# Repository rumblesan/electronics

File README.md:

# Electronics Projects

KiCAD projects for electronics stuff I'm working on.

## Description

Mostly Serge/CGS synth stuff currently, with all original circuits designed by Serge Tcherepnin and Ken Stone.

## Contact

Drop me an email at guy@rumblesan.com

## License

Creative Commons Attribution 4.0 International License

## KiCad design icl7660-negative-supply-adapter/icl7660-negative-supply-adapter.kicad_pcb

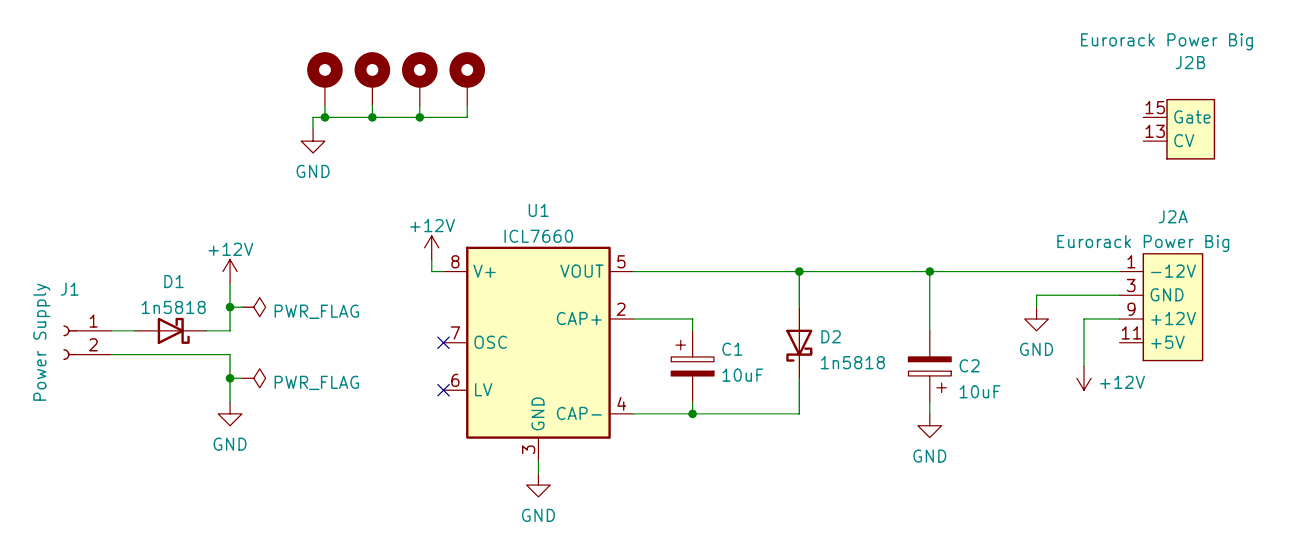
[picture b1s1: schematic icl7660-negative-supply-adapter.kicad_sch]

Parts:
C1, C2: 10uF; CP_Radial_D5.0mm_P2.00mm; Tolerance 20%; Voltage 50v
D1, D2: 1n5818; D_DO-41_SOD81_P10.16mm_Horizontal
H1, H2, H3, H4: MountingHole_Pad; MountingHole_3.2mm_M3_DIN965_Pad
J1: Power Supply; PinHeader_1x02_P2.54mm_Vertical
J2: Eurorack Power Big; Eurorack_PowerHeader_2x08_P2.54mm_Shrouded
U1: ICL7660; DIP-8_W7.62mm_Socket

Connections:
+12V: D1.1 (K), J2.9 (+12V), J2.10 (+12V), U1.8 (V+)
GND: C2.1, H1.1, H2.1, H3.1, H4.1, J1.2, J2.3 (GND), J2.4 (GND), J2.5 (GND), J2.6 (GND), J2.7 (GND), J2.8 (GND), U1.3 (GND)
unnamed: C1.1, U1.2 (CAP+)
unnamed: C1.2, D2.1 (K), U1.4 (CAP-)
unnamed: C2.2, D2.2 (A), J2.1 (-12V), J2.2 (-12V), U1.5 (VOUT)
unnamed: D1.2 (A), J1.1
unnamed: J2.11 (+5V), J2.12 (+5V)
unnamed: J2.13 (CV), J2.14 (CV)
unnamed: J2.15 (Gate), J2.16 (Gate)

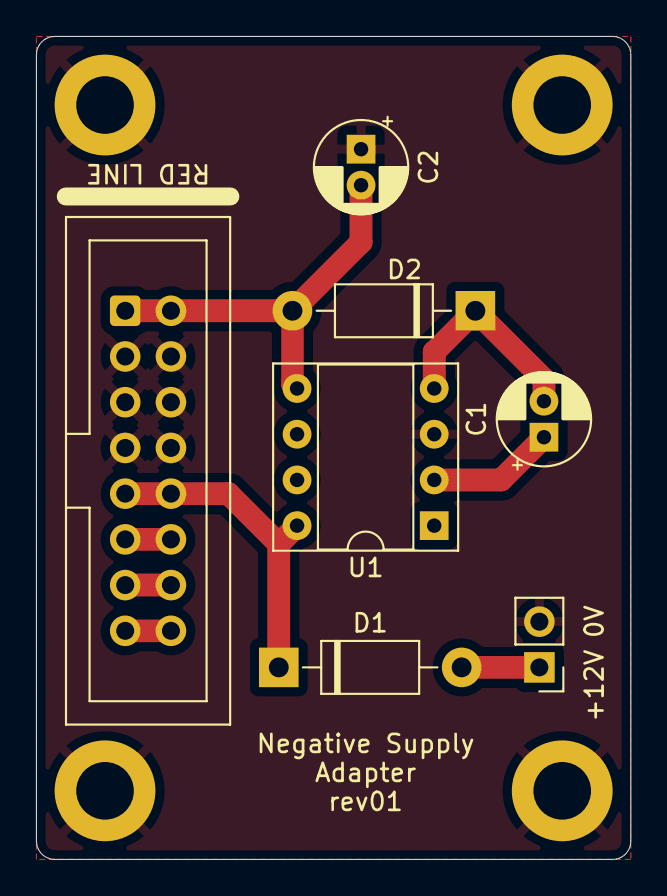
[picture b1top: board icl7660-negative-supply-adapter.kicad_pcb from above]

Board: 2 copper layers, 33.0 x 45.7 mm, 11 parts (0 on the bottom side), 9 nets.

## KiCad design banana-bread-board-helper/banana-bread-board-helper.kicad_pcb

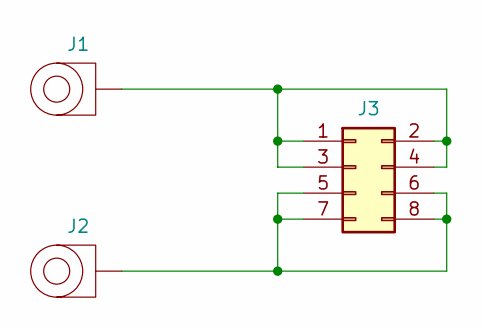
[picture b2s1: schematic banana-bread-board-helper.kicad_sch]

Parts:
J1, J2: BananaJack_PCBMount; Deltron_571_PCB_BananaJack
J3: Conn_02x04_Odd_Even; PinHeader_2x04_P2.54mm_Vertical

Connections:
unnamed: J1.1, J3.1, J3.2, J3.3, J3.4
unnamed: J2.1, J3.5, J3.6, J3.7, J3.8

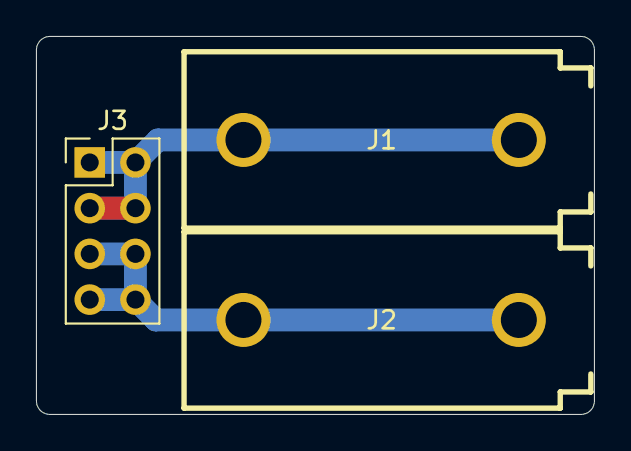
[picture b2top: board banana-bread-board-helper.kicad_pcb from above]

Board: 2 copper layers, 31.0 x 21.0 mm, 3 parts (0 on the bottom side), 2 nets.

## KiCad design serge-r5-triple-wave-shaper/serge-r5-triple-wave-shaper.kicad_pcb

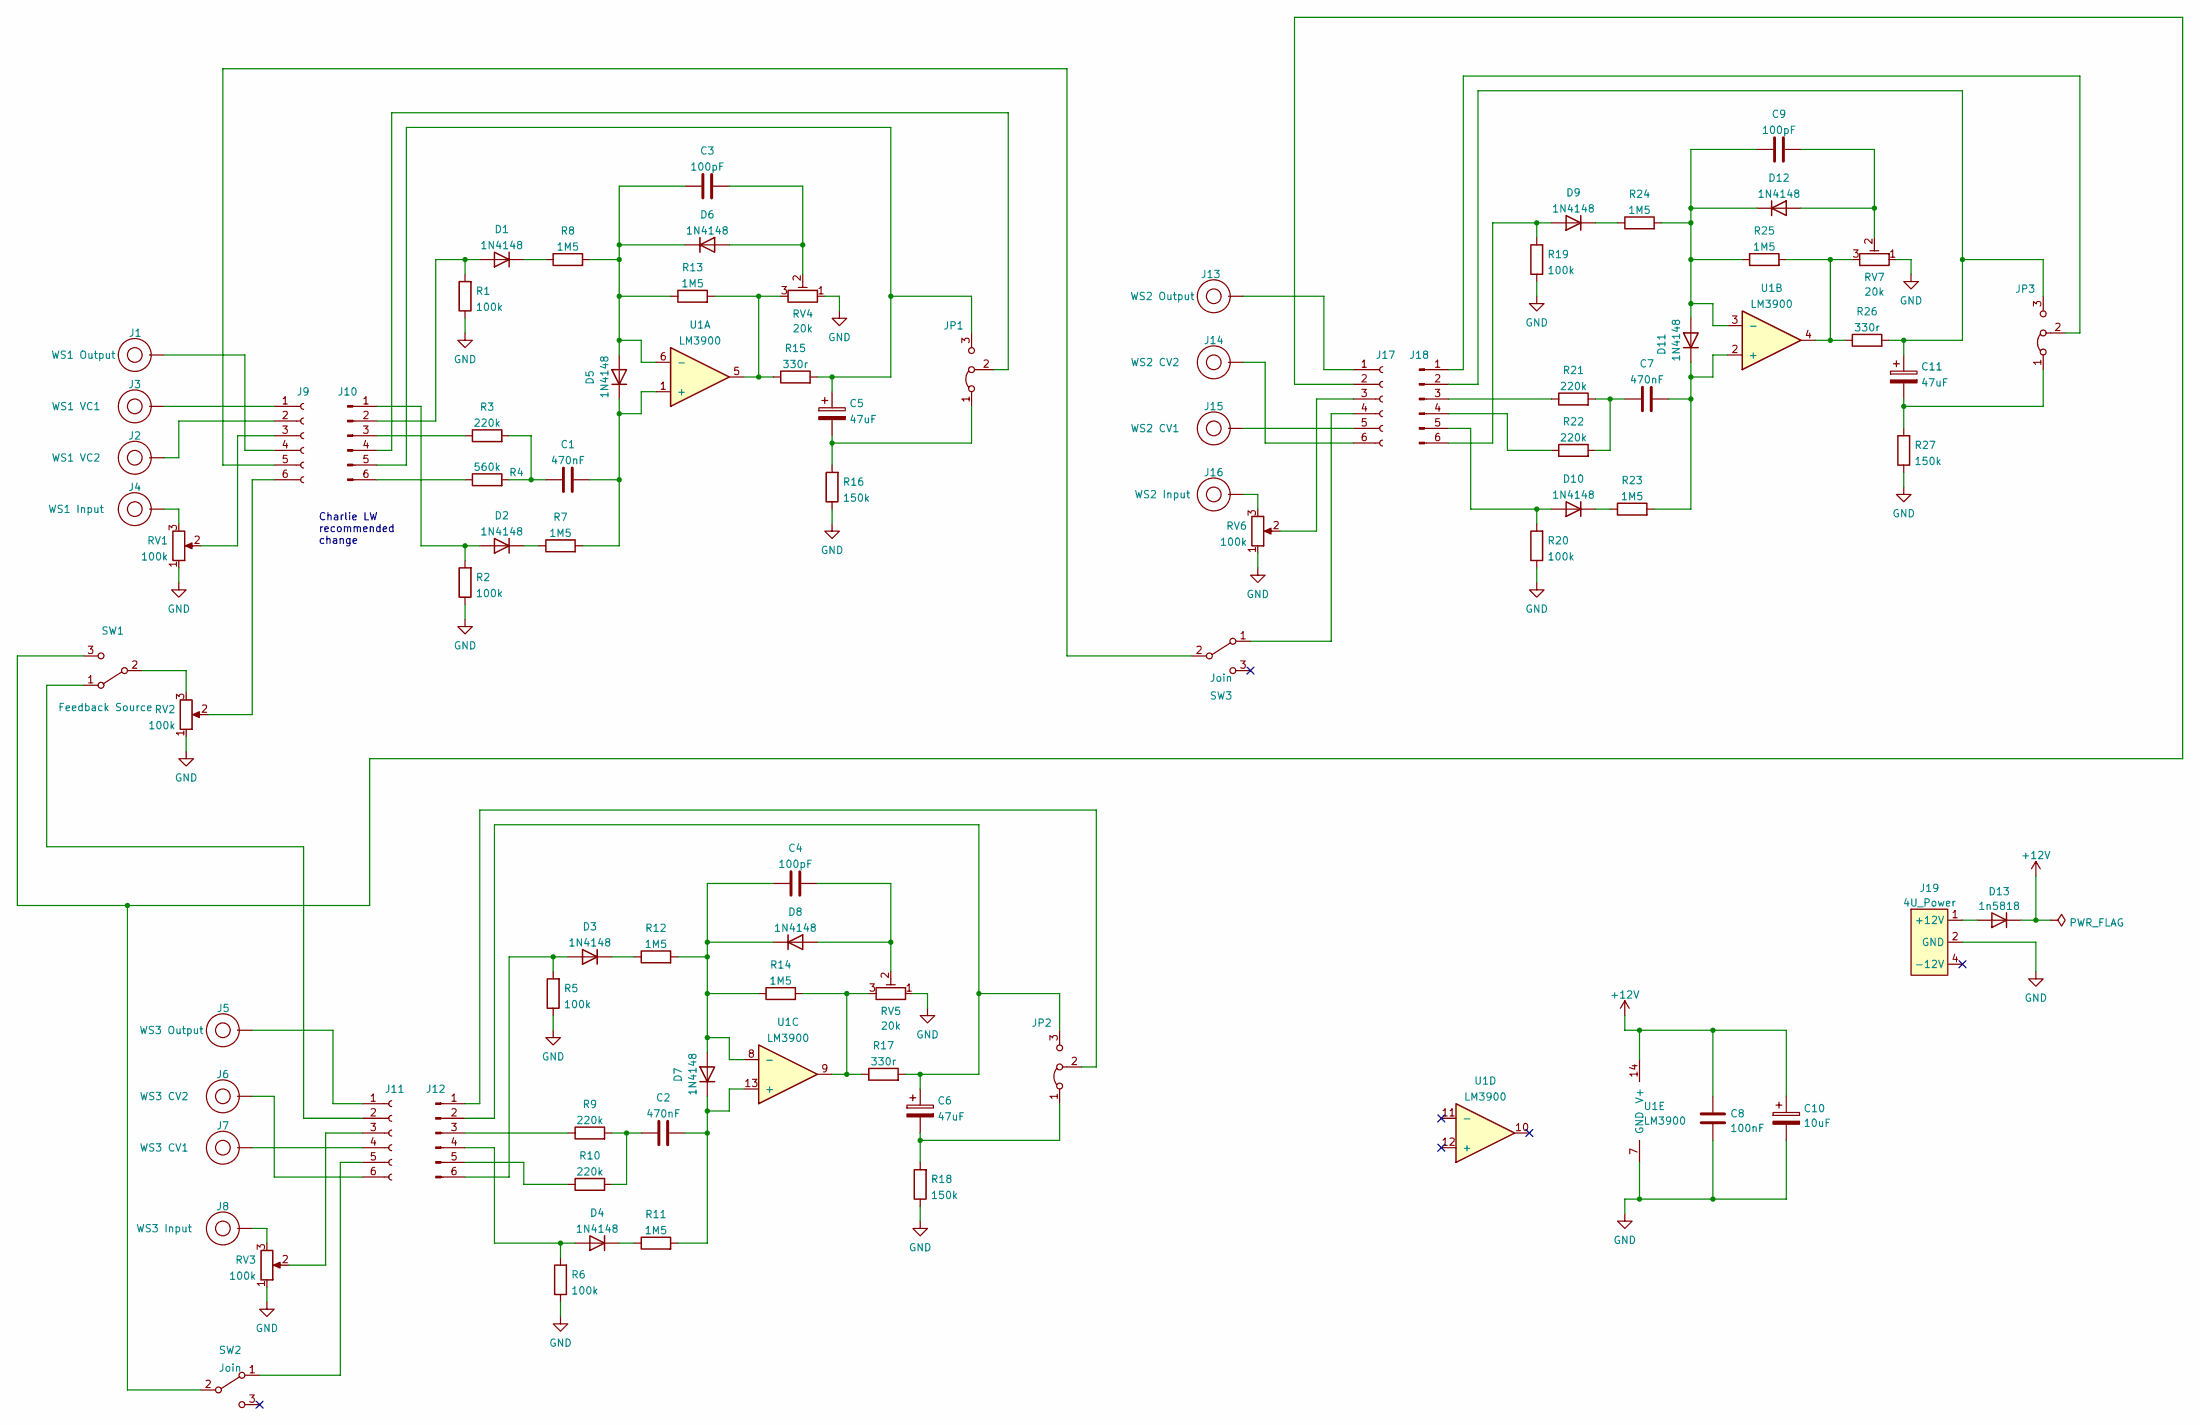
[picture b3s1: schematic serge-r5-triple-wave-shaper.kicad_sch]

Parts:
C1, C2, C7: 470nF; C_Rect_L7.0mm_W3.5mm_P5.00mm; Tolerance 5%
C3, C4, C9: 100pF; C_Rect_L7.0mm_W3.5mm_P5.00mm; Tolerance 5%
C5, C6, C11: 47uF; CP_Radial_D5.0mm_P2.00mm; Tolerance 20%; Voltage 50v
C8: 100nF; C_Rect_L7.0mm_W3.5mm_P5.00mm; Tolerance 5%
C10: 10uF; CP_Radial_D5.0mm_P2.00mm; Tolerance 20%; Voltage 50v
D1, D2, D3, D4, D5, D6, D7, D8, D9, D10, D11, D12: 1N4148; D_DO-35_SOD27_P7.62mm_Horizontal
D13: 1n5818; D_DO-41_SOD81_P10.16mm_Horizontal
J1, J2, J3, J4, J5, J6, J7, J8, J13, J14, J15, J16: Banana Socket PanelMount; BananaJack_THT_JohnsonCinch_108-09
J9, J11, J17: Conn_01x06_Female; PinSocket_1x06_P2.54mm_Vertical
J10, J12, J18: Conn_01x06_Male; PinHeader_1x06_P2.54mm_Vertical
J19: 4U_Power; 4u_Power_Molex_KK-254_P2.54mm
JP1, JP2, JP3: Jumper_3_Bridged12; PinHeader_1x03_P2.54mm_Vertical
R1, R2, R5, R6, R19, R20: 100k; R_Axial_DIN0207_L6.3mm_D2.5mm_P10.16mm_Horizontal; Tolerance 1%
R3, R9, R10, R21, R22: 220k; R_Axial_DIN0207_L6.3mm_D2.5mm_P10.16mm_Horizontal; Tolerance 1%
R4: 560k; R_Axial_DIN0207_L6.3mm_D2.5mm_P10.16mm_Horizontal; Tolerance 1%
R7, R8, R11, R12, R13, R14, R23, R24, R25: 1M5; R_Axial_DIN0207_L6.3mm_D2.5mm_P10.16mm_Horizontal; Tolerance 1%
R15, R17, R26: 330r; R_Axial_DIN0207_L6.3mm_D2.5mm_P10.16mm_Horizontal; Tolerance 1%
R16, R18, R27: 150k; R_Axial_DIN0207_L6.3mm_D2.5mm_P10.16mm_Horizontal; Tolerance 1%
RV1, RV2, RV3, RV6: 100k; Potentiometer_Alpha_RD901F-40-00D_Single_Vertical
RV4, RV5, RV7: 20k; Potentiometer_THT_Bourns_3306P_Vertical
SW1, SW2, SW3: SW_SPDT; Toggle_Switch_100SP1T1B3M2QE
U1: LM3900; DIP-14_W7.62mm_Socket

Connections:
+12V: C8.1, C10.1, D13.1 (K), U1.14 (V+)
GND: C8.2, C10.2, J19.2 (GND), J19.3 (GND), R1.1, R2.1, R5.1, R6.1, R16.1, R18.1, R19.1, R20.1, R27.1, RV1.1, RV2.1, RV3.1, RV4.1, RV5.1, RV6.1, RV7.1, U1.7 (GND)
unnamed: C1.1, R3.2, R4.2
unnamed: C1.2, D5.1 (K), R7.2, U1.1 (+)
unnamed: C2.1, R9.2, R10.2
unnamed: C2.2, D7.1 (K), R11.2, U1.13 (+)
unnamed: C3.1, D5.2 (A), D6.1 (K), R8.2, R13.1, U1.6 (-)
unnamed: C3.2, D6.2 (A), RV4.2
unnamed: C4.1, D7.2 (A), D8.1 (K), R12.2, R14.1, U1.8 (-)
unnamed: C4.2, D8.2 (A), RV5.2
unnamed: C5.1, J10.5, JP1.3 (B), R15.2
unnamed: C5.2, JP1.1 (A), R16.2
unnamed: C6.1, J12.2, JP2.3 (B), R17.2
unnamed: C6.2, JP2.1 (A), R18.2
unnamed: C7.1, R21.2, R22.2
unnamed: C7.2, D11.1 (K), R23.2, U1.2 (+)
unnamed: C9.1, D11.2 (A), D12.1 (K), R24.2, R25.1, U1.3 (-)
unnamed: C9.2, D12.2 (A), RV7.2
unnamed: C11.1, J18.2, JP3.3 (B), R26.2
unnamed: C11.2, JP3.1 (A), R27.2
unnamed: D1.1 (K), R8.1
unnamed: D1.2 (A), J10.2, R1.2
unnamed: D2.1 (K), R7.1
unnamed: D2.2 (A), J10.1, R2.2
unnamed: D3.1 (K), R12.1
unnamed: D3.2 (A), J12.6, R5.2
unnamed: D4.1 (K), R11.1
unnamed: D4.2 (A), J12.4, R6.2
unnamed: D9.1 (K), R24.1
unnamed: D9.2 (A), J18.6, R19.2
unnamed: D10.1 (K), R23.1
unnamed: D10.2 (A), J18.5, R20.2
unnamed: D13.2 (A), J19.1 (+12V)
unnamed: J1.1, J9.4
unnamed: J2.1, J9.2
unnamed: J3.1, J9.1
unnamed: J4.1, RV1.3
unnamed: J8.1, RV3.3
unnamed: J9.3, RV1.2
unnamed: J9.5, SW3.2 (B)
unnamed: J9.6, RV2.2
unnamed: J10.3, R3.1
unnamed: J10.4, JP1.2 (C)
unnamed: J10.6, R4.1
unnamed: J5.1, J11.1
unnamed: J11.2, SW1.1 (A)
unnamed: J11.3, RV3.2
unnamed: J7.1, J11.4
unnamed: J11.5, SW2.1 (A)
unnamed: J6.1, J11.6
unnamed: J12.1, JP2.2 (C)
unnamed: J12.3, R9.1
unnamed: J12.5, R10.1
unnamed: J13.1, J17.1
unnamed: J14.1, J17.6
unnamed: J15.1, J17.5
unnamed: J16.1, RV6.3
unnamed: J17.2, SW1.3 (C), SW2.2 (B)
unnamed: J17.3, RV6.2
unnamed: J17.4, SW3.1 (A)
unnamed: J18.1, JP3.2 (C)
unnamed: J18.3, R21.1
unnamed: J18.4, R22.1
unnamed: R13.2, R15.1, RV4.3, U1.5
unnamed: R14.2, R17.1, RV5.3, U1.9
unnamed: R25.2, R26.1, RV7.3, U1.4
unnamed: RV2.3, SW1.2 (B)

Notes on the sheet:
Charlie LW recommended change

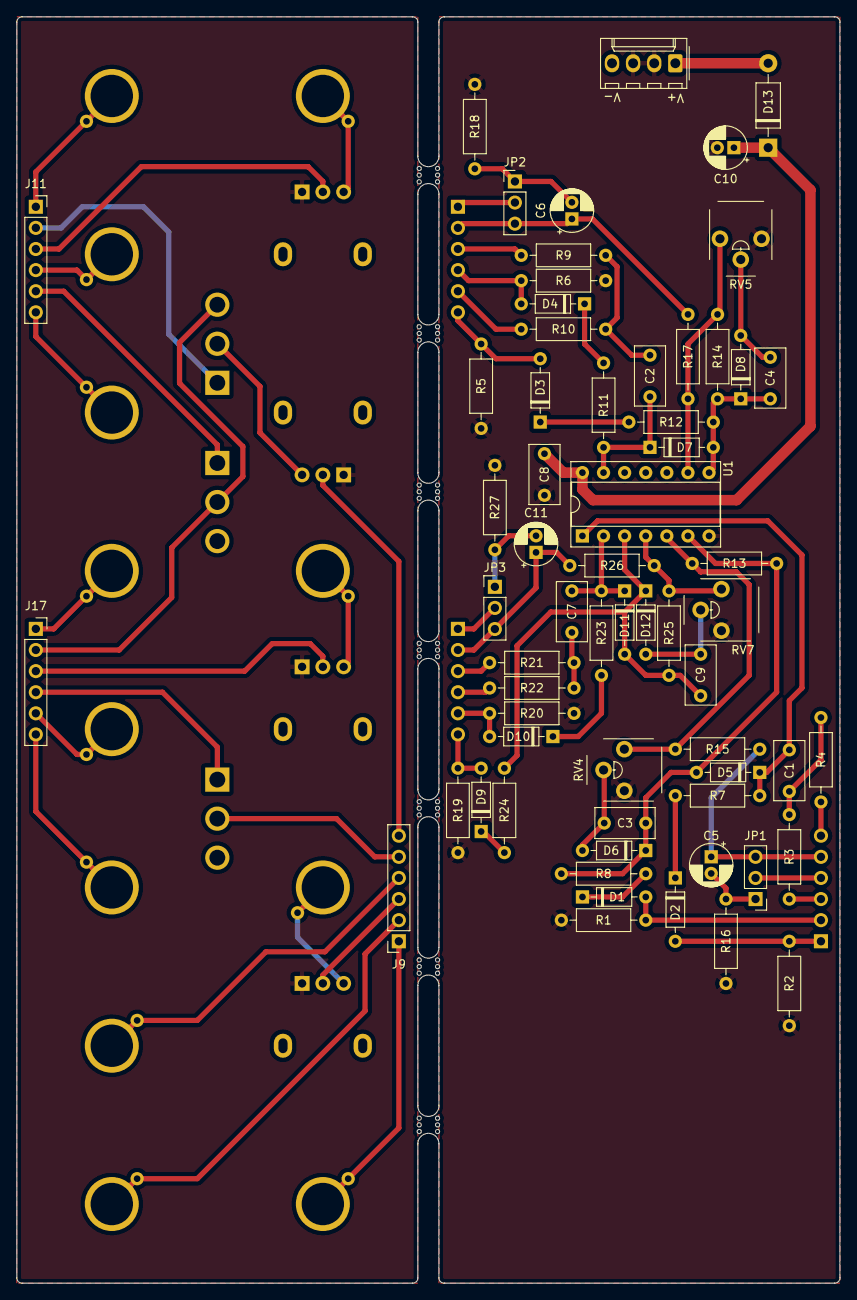
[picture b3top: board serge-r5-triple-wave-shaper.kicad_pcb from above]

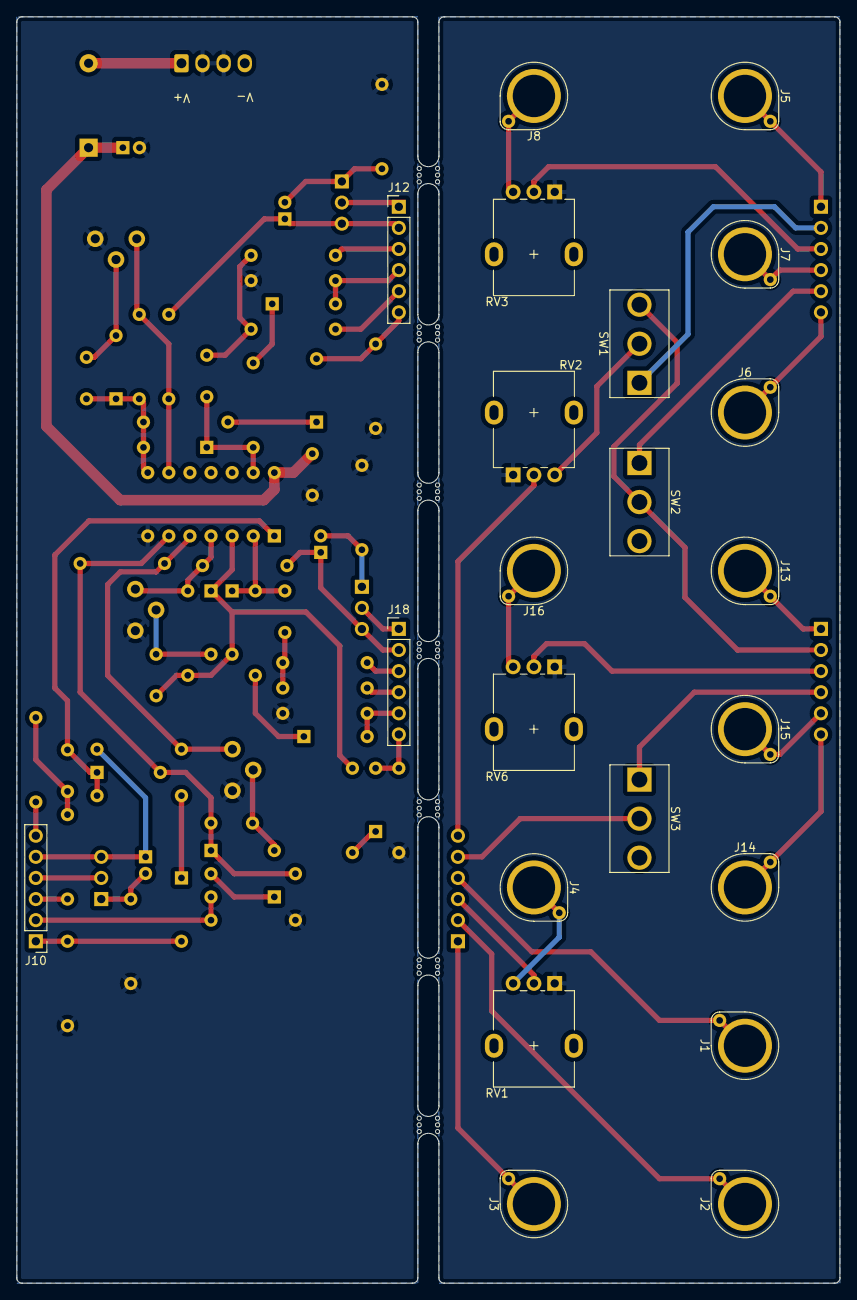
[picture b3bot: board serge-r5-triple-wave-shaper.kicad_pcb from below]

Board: 2 copper layers, 99.1 x 152.4 mm, 91 parts (22 on the bottom side), 67 nets.

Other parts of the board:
mouse-bite-2.54mm-slot, mouse-bite-2.54mm-slot#2, mouse-bite-2.54mm-slot#3, mouse-bite-2.54mm-slot#4, mouse-bite-2.54mm-slot#5, mouse-bite-2.54mm-slot#6, mouse-bite-2.54mm-slot#7: VAL**; mouse-bite-2.54mm-slot

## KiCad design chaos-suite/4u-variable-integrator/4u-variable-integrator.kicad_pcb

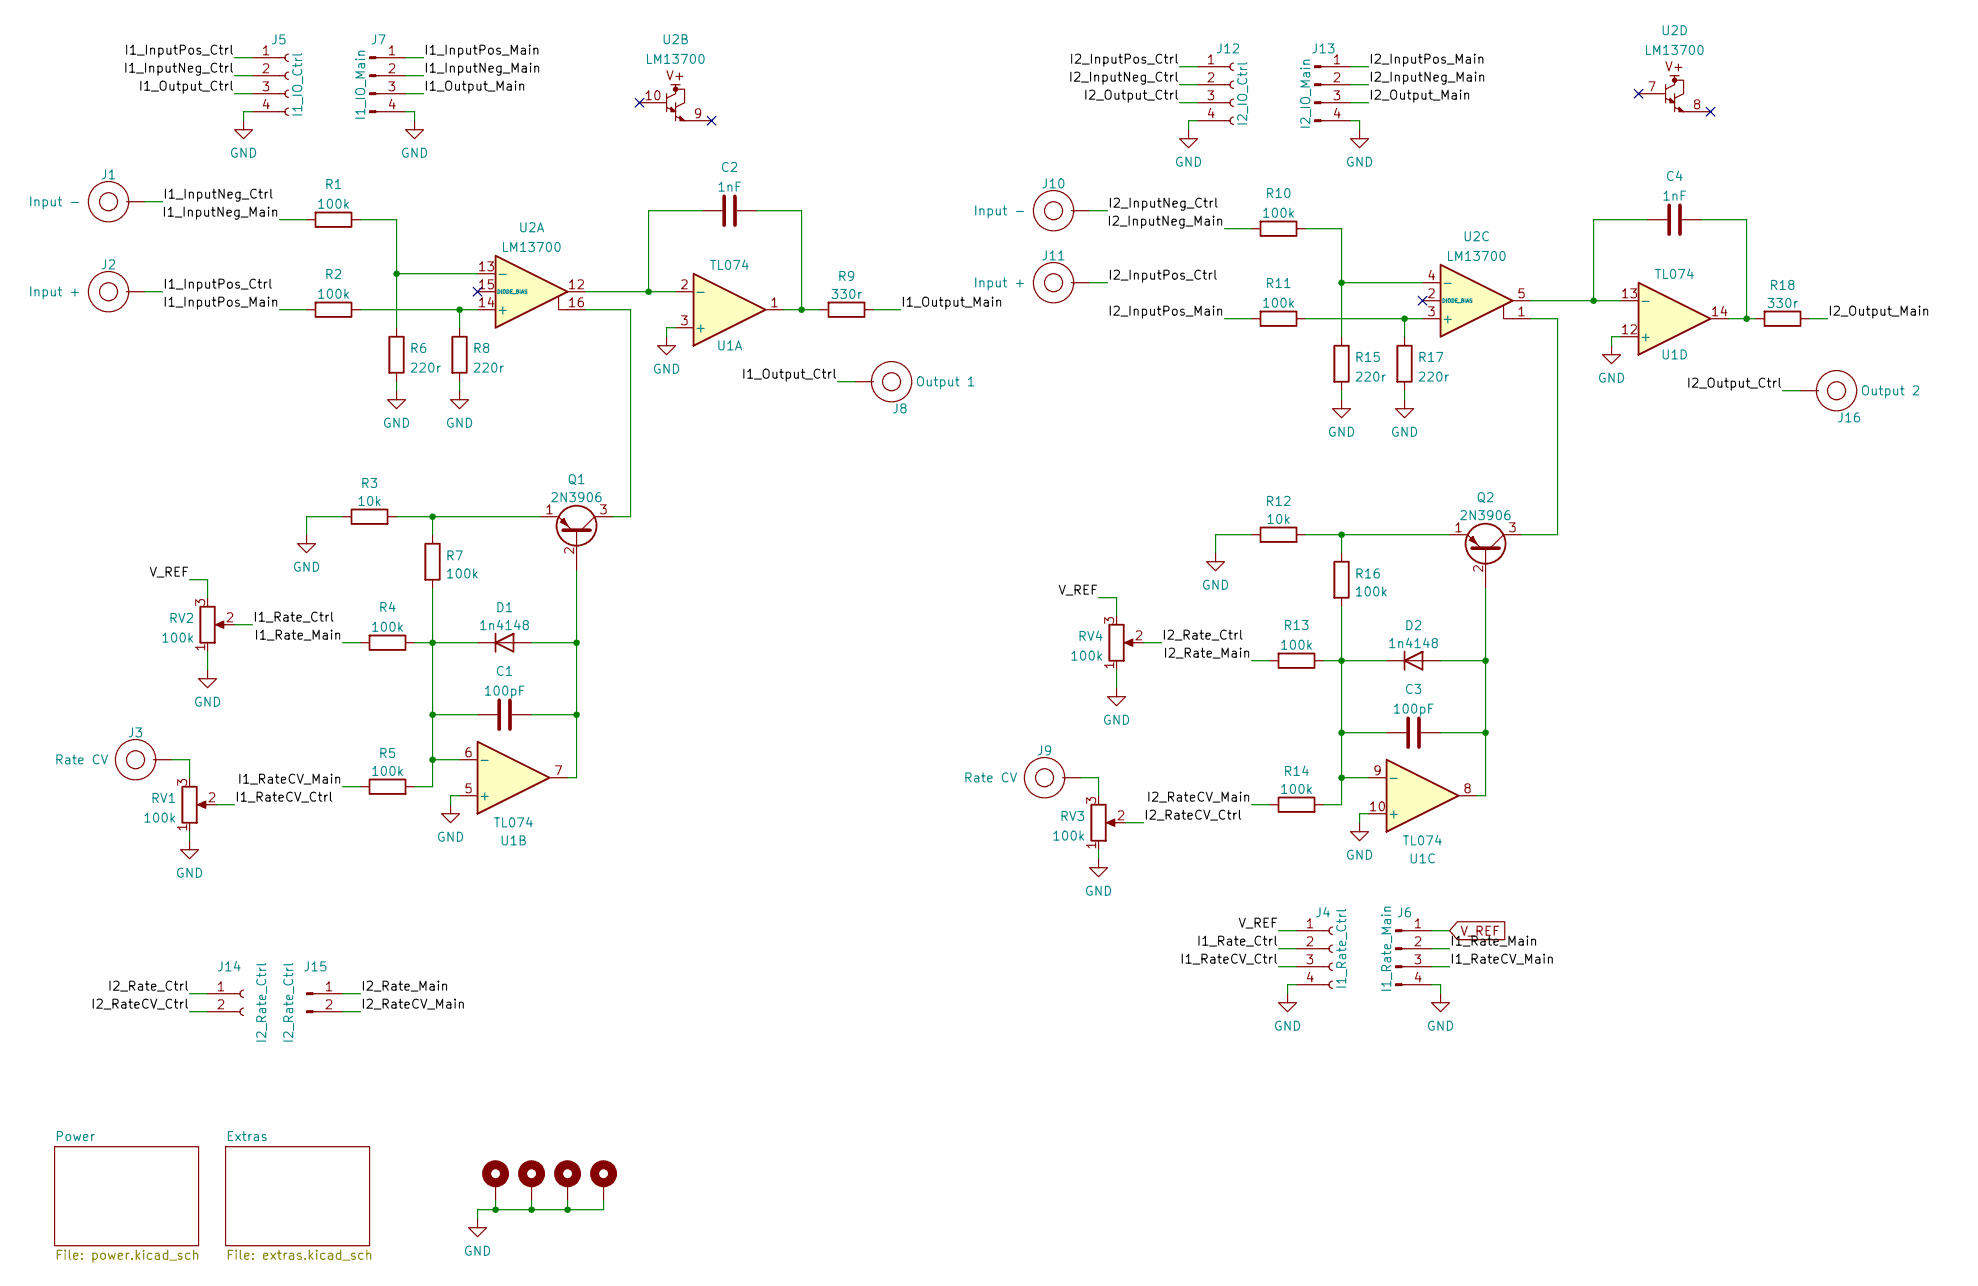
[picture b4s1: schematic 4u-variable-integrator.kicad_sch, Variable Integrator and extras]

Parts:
C1, C3: 100pF; C_Rect_L7.0mm_W3.5mm_P5.00mm
C2, C4: 1nF; C_Rect_L7.0mm_W3.5mm_P5.00mm
D1, D2: 1n4148; D_DO-35_SOD27_P7.62mm_Horizontal
H1, H2, H3, H4: MountingHole_Pad; MountingHole_3.2mm_M3_DIN965_Pad
J1, J2, J3, J8, J9, J10, J11, J16: Banana Socket PanelMount; BananaJack_THT_JohnsonCinch_108-09
J4, J5, J12: Conn_01x04_Female; PinSocket_1x04_P2.54mm_Vertical
J6, J7, J13: Conn_01x04_Male; PinHeader_1x04_P2.54mm_Vertical
J14: Conn_01x02_Female; PinSocket_1x02_P2.54mm_Vertical
J15: Conn_01x02_Male; PinHeader_1x02_P2.54mm_Vertical
Q1, Q2: 2N3906; TO-92_Inline_Wide
R1, R2, R4, R5, R7, R10, R11, R13, R14, R16: 100k; R_Axial_DIN0207_L6.3mm_D2.5mm_P10.16mm_Horizontal; Tolerance 1%
R3, R12: 10k; R_Axial_DIN0207_L6.3mm_D2.5mm_P10.16mm_Horizontal; Tolerance 1%
R6, R8, R15, R17: 220r; R_Axial_DIN0207_L6.3mm_D2.5mm_P10.16mm_Horizontal; Tolerance 1%
R9, R18: 330r; R_Axial_DIN0207_L6.3mm_D2.5mm_P10.16mm_Horizontal; Tolerance 1%
RV1, RV2, RV3, RV4: 100k; Potentiometer_Alpha_RD901F-40-00D_Single_Vertical
U1: TL074; DIP-14_W7.62mm_Socket
U2: LM13700; DIP-16_W7.62mm_Socket

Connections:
/I1_InputNeg_Ctrl: J1.1, J5.2
/I1_InputNeg_Main: J7.2, R1.2
/I1_InputPos_Ctrl: J2.1, J5.1
/I1_InputPos_Main: J7.1, R2.2
/I1_Output_Ctrl: J5.3, J8.1
/I1_Output_Main: J7.3, R9.1
/I1_RateCV_Ctrl: J4.3, RV1.2
/I1_RateCV_Main: J6.3, R5.1
/I1_Rate_Ctrl: J4.2, RV2.2
/I1_Rate_Main: J6.2, R4.2
/I2_InputNeg_Ctrl: J10.1, J12.2
/I2_InputNeg_Main: J13.2, R10.2
/I2_InputPos_Ctrl: J11.1, J12.1
/I2_InputPos_Main: J13.1, R11.2
/I2_Output_Ctrl: J12.3, J16.1
/I2_Output_Main: J13.3, R18.1
/I2_RateCV_Ctrl: J14.2, RV3.2
/I2_RateCV_Main: J15.2, R14.1
/I2_Rate_Ctrl: J14.1, RV4.2
/I2_Rate_Main: J15.1, R13.2
GND: H1.1, H2.1, H3.1, H4.1, J4.4, J5.4, J6.4, J7.4, J12.4, J13.4, R3.1, R6.2, R8.2, R12.1, R15.2, R17.2, RV1.1, RV2.1, RV3.1, RV4.1, U1.3 (+), U1.5 (+), U1.10 (+), U1.12 (+); also elsewhere on the board
unnamed: C1.1, D1.1 (K), R4.1, R5.2, R7.2, U1.6 (-)
unnamed: C1.2, D1.2 (A), Q1.2 (B), U1.7
unnamed: C2.1, U1.2 (-), U2.12
unnamed: C2.2, R9.2, U1.1
unnamed: C3.1, D2.1 (K), R13.1, R14.2, R16.2, U1.9 (-)
unnamed: C3.2, D2.2 (A), Q2.2 (B), U1.8
unnamed: C4.1, U1.13 (-), U2.5
unnamed: C4.2, R18.2, U1.14
unnamed: J3.1, RV1.3
unnamed: J9.1, RV3.3
unnamed: Q1.1 (E), R3.2, R7.1
unnamed: Q1.3 (C), U2.16
unnamed: Q2.1 (E), R12.2, R16.1
unnamed: Q2.3 (C), U2.1
unnamed: R1.1, R6.1, U2.13 (-)
unnamed: R2.1, R8.1, U2.14 (+)
unnamed: R10.1, R15.1, U2.4 (-)
unnamed: R11.1, R17.1, U2.3 (+)
V_REF: J4.1, J6.1, RV2.3, RV4.3; also elsewhere on the board

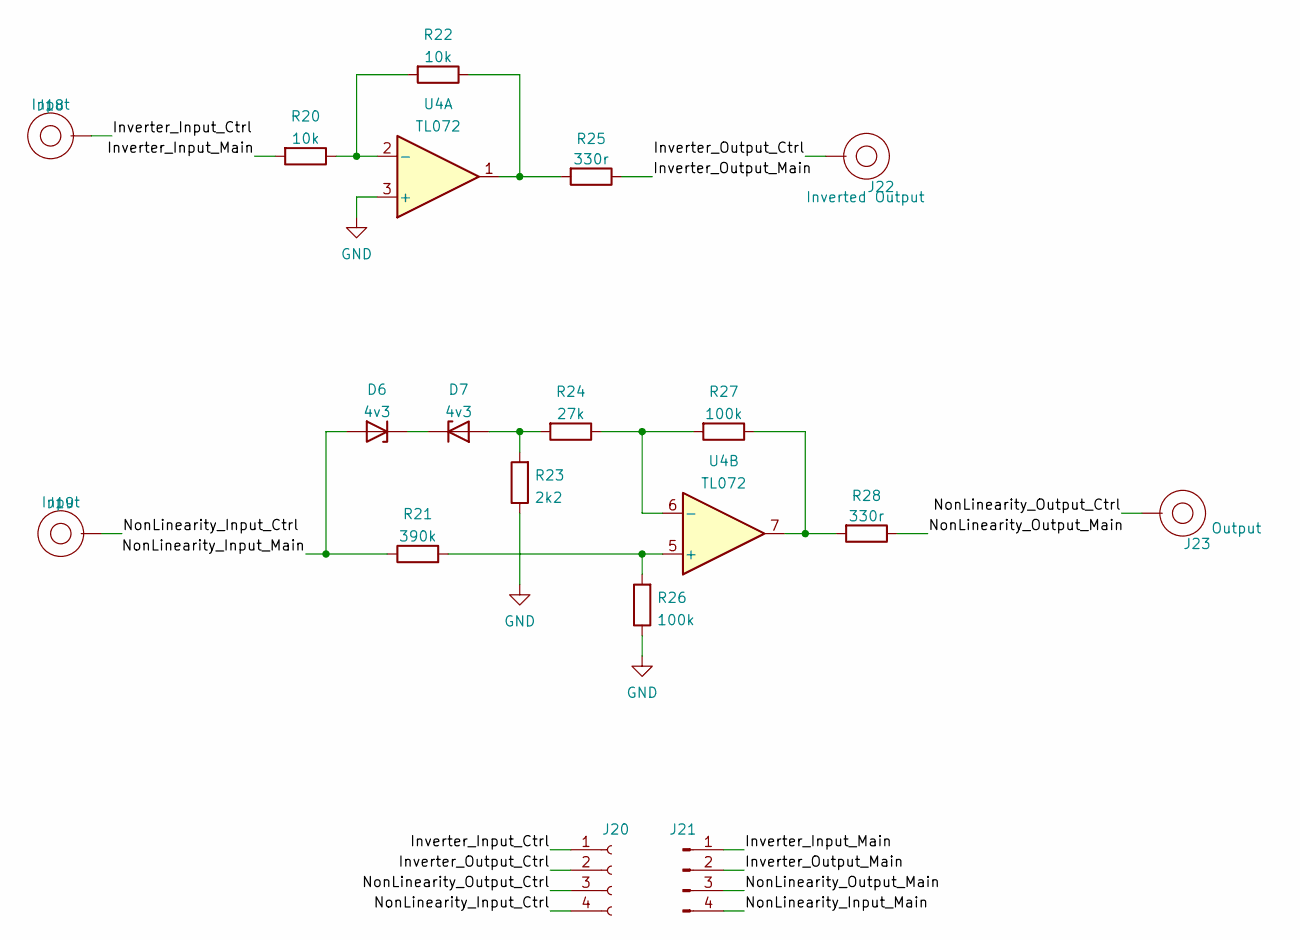
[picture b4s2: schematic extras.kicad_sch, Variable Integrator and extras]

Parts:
D6, D7: 4v3; D_DO-35_SOD27_P7.62mm_Horizontal
J18, J19, J22, J23: Banana Socket PanelMount; BananaJack_THT_JohnsonCinch_108-09
J20: Conn_01x04_Female; PinSocket_1x04_P2.54mm_Vertical
J21: Conn_01x04_Male; PinHeader_1x04_P2.54mm_Vertical
R20, R22: 10k; R_Axial_DIN0207_L6.3mm_D2.5mm_P10.16mm_Horizontal; Tolerance 1%
R21: 390k; R_Axial_DIN0207_L6.3mm_D2.5mm_P10.16mm_Horizontal; Tolerance 1%
R23: 2k2; R_Axial_DIN0207_L6.3mm_D2.5mm_P10.16mm_Horizontal; Tolerance 1%
R24: 27k; R_Axial_DIN0207_L6.3mm_D2.5mm_P10.16mm_Horizontal; Tolerance 1%
R25, R28: 330r; R_Axial_DIN0207_L6.3mm_D2.5mm_P10.16mm_Horizontal; Tolerance 1%
R26, R27: 100k; R_Axial_DIN0207_L6.3mm_D2.5mm_P10.16mm_Horizontal; Tolerance 1%
U4: TL072; DIP-8_W7.62mm_Socket

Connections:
/Extras/Inverter_Input_Ctrl: J18.1, J20.1
/Extras/Inverter_Input_Main: J21.1, R20.2
/Extras/Inverter_Output_Ctrl: J20.2, J22.1
/Extras/Inverter_Output_Main: J21.2, R25.1
/Extras/NonLinearity_Input_Ctrl: J19.1, J20.4
/Extras/NonLinearity_Input_Main: D6.2 (A), J21.4, R21.1
/Extras/NonLinearity_Output_Ctrl: J20.3, J23.1
/Extras/NonLinearity_Output_Main: J21.3, R28.1
GND: R23.1, R26.1, U4.3 (+); also elsewhere on the board
unnamed: D6.1 (K), D7.1 (K)
unnamed: D7.2 (A), R23.2, R24.2
unnamed: R20.1, R22.2, U4.2 (-)
unnamed: R21.2, R26.2, U4.5 (+)
unnamed: R22.1, R25.2, U4.1
unnamed: R24.1, R27.2, U4.6 (-)
unnamed: R27.1, R28.2, U4.7

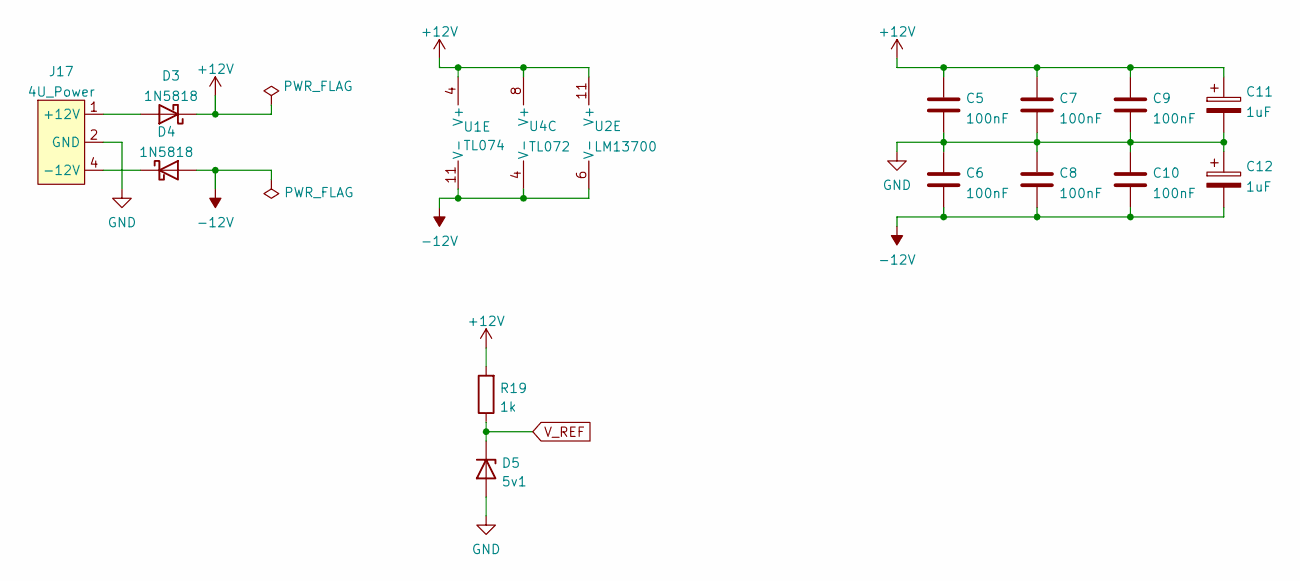
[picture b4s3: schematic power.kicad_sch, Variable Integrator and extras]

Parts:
C5, C6, C7, C8, C9, C10: 100nF; C_Rect_L7.0mm_W3.5mm_P5.00mm
C11, C12: 1uF; CP_Radial_D5.0mm_P2.00mm
D3, D4: 1N5818; D_DO-41_SOD81_P10.16mm_Horizontal
D5: 5v1; D_DO-35_SOD27_P7.62mm_Horizontal
J17: 4U_Power; 4u_Power_Molex_KK-254_P2.54mm
R19: 1k; R_Axial_DIN0207_L6.3mm_D2.5mm_P10.16mm_Horizontal; Tolerance 1%
U1: TL074; DIP-14_W7.62mm_Socket
U2: LM13700; DIP-16_W7.62mm_Socket
U4: TL072; DIP-8_W7.62mm_Socket

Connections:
+12V: C5.1, C7.1, C9.1, C11.1, D3.1 (K), R19.2, U1.4 (V+), U2.11 (V+), U4.8 (V+)
-12V: C6.2, C8.2, C10.2, C12.2, D4.2 (A), U1.11 (V-), U2.6 (V-), U4.4 (V-)
GND: C5.2, C6.1, C7.2, C8.1, C9.2, C10.1, C11.2, C12.1, D5.2 (A), J17.2 (GND), J17.3 (GND); also elsewhere on the board
unnamed: D3.2 (A), J17.1 (+12V)
unnamed: D4.1 (K), J17.4 (-12V)
V_REF: D5.1 (K), R19.1; also elsewhere on the board

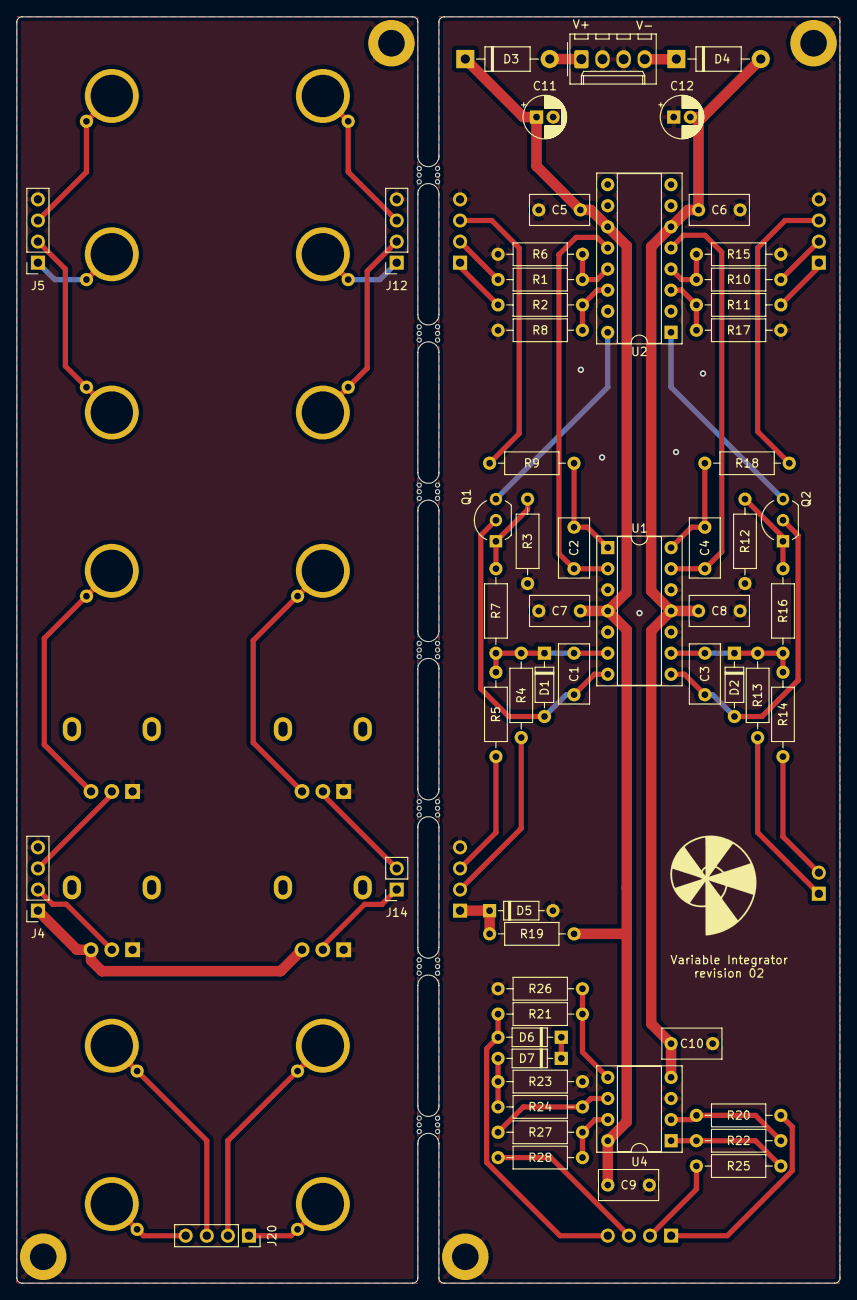
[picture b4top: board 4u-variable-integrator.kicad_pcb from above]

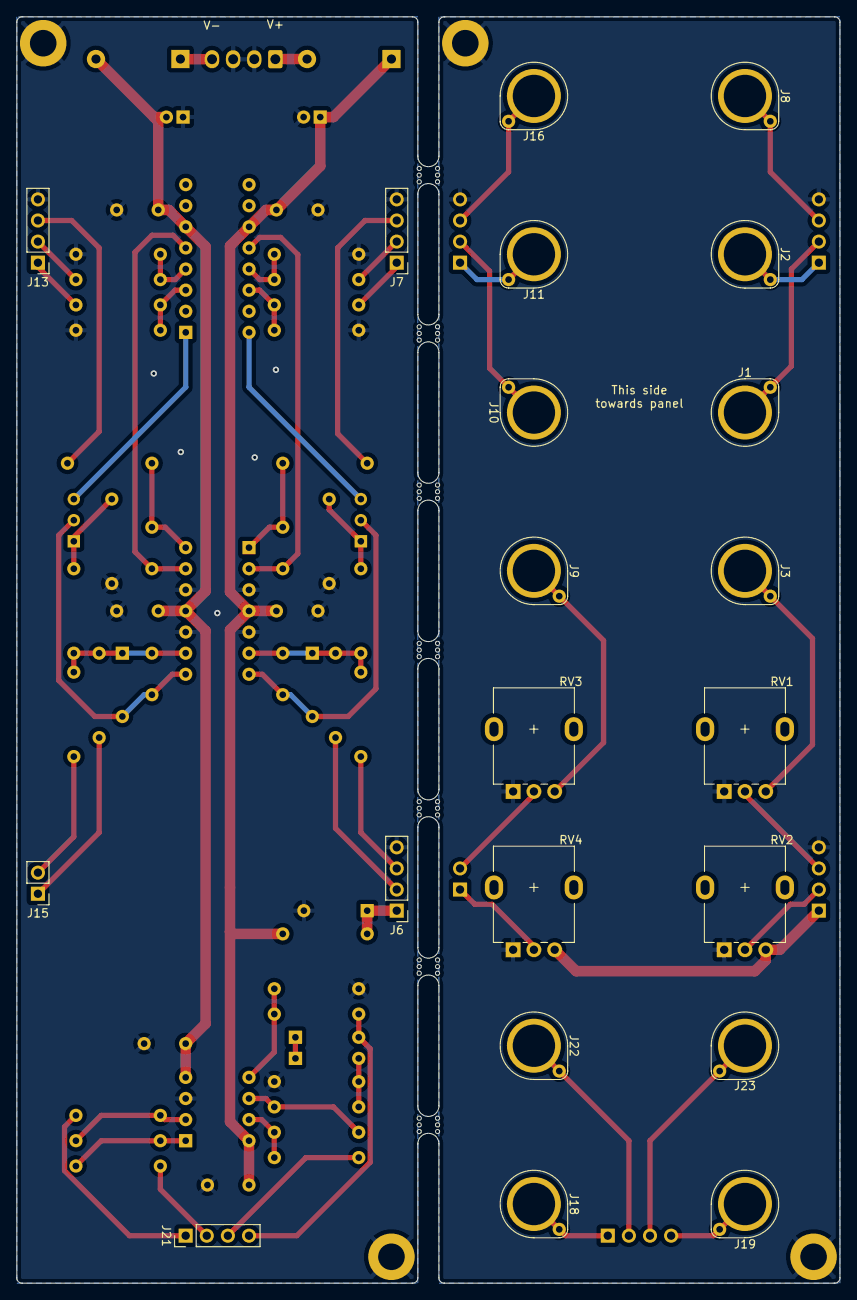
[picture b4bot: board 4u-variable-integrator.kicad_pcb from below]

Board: 2 copper layers, 99.1 x 152.4 mm, 90 parts (21 on the bottom side), 59 nets.

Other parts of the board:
mouse-bite-2.54mm-slot, mouse-bite-2.54mm-slot#2, mouse-bite-2.54mm-slot#3, mouse-bite-2.54mm-slot#4, mouse-bite-2.54mm-slot#5, mouse-bite-2.54mm-slot#6, mouse-bite-2.54mm-slot#7: VAL**; mouse-bite-2.54mm-slot

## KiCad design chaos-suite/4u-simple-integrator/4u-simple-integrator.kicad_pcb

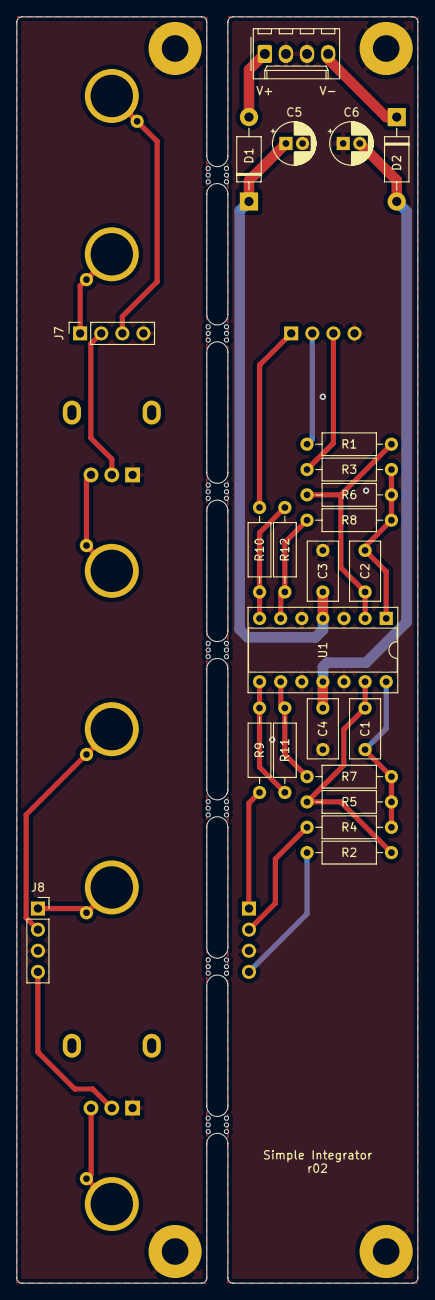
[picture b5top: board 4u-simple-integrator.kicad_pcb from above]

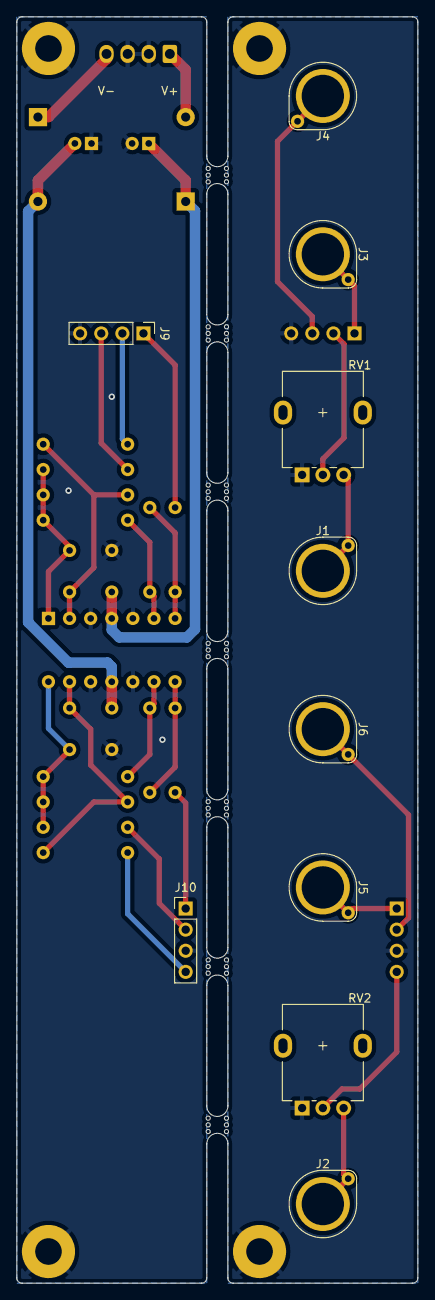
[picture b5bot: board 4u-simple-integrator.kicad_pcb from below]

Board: 2 copper layers, 48.3 x 152.4 mm, 45 parts (10 on the bottom side), 27 nets.

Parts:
C1, C2: 1nF; C_Rect_L7.0mm_W3.5mm_P5.00mm
C3, C4: 100nF; C_Rect_L7.0mm_W3.5mm_P5.00mm
C5, C6: 10uF; CP_Radial_D5.0mm_P2.00mm
D1, D2: 1N5818; D_DO-41_SOD81_P10.16mm_Horizontal
H1, H2, H3, H4: MountingHole_Pad; MountingHole_3.2mm_M3_Pad
J1, J2, J3, J4, J5, J6: BananaJack_PanelMount; BananaJack_THT_JohnsonCinch_108-09
J7: I2_Ctrl; PinSocket_1x04_P2.54mm_Vertical
J8: I1_Ctrl; PinSocket_1x04_P2.54mm_Vertical
J9: I2_Main; PinHeader_1x04_P2.54mm_Vertical
J10: I1_Main; PinHeader_1x04_P2.54mm_Vertical
J11: 4U_Power; 4u_Power_Molex_KK-254_P2.54mm
R1, R2: 100k; R_Axial_DIN0207_L6.3mm_D2.5mm_P10.16mm_Horizontal
R3, R4, R9, R10: 330r; R_Axial_DIN0207_L6.3mm_D2.5mm_P10.16mm_Horizontal
R5, R6: 100k (optional); R_Axial_DIN0207_L6.3mm_D2.5mm_P10.16mm_Horizontal
R7, R8, R11, R12: 10k; R_Axial_DIN0207_L6.3mm_D2.5mm_P10.16mm_Horizontal
RV1, RV2: 100k; Potentiometer_Alpha_RD901F-40-00D_Single_Vertical
U1: TL074; DIP-14_W7.62mm_Socket
mouse-bite-2.54mm-slot, mouse-bite-2.54mm-slot#2, mouse-bite-2.54mm-slot#3, mouse-bite-2.54mm-slot#4, mouse-bite-2.54mm-slot#5, mouse-bite-2.54mm-slot#6, mouse-bite-2.54mm-slot#7: VAL**; mouse-bite-2.54mm-slot

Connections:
+12V: C3.1, C5.1, D1.1 (K), U1.4 (V+)
-12V: C4.2, C6.2, D2.2 (A), U1.11 (V-)
GND: C3.2, C4.1, C5.2, C6.1, H1.1, H2.1, H3.1, H4.1, J7.4, J8.3, J9.4, J10.3, J11.2 (GND), J11.3 (GND), RV1.1, RV2.1, U1.3 (+), U1.5 (+), U1.10 (+), U1.12 (+)
unnamed: C1.1, R2.1, R5.2, U1.13 (-)
unnamed: C1.2, R4.2, R5.1, R7.2, U1.14
unnamed: C2.1, R1.1, R6.2, U1.2 (-)
unnamed: C2.2, R3.2, R6.1, R8.2, U1.1
unnamed: D1.2 (A), J11.1 (+12V)
unnamed: D2.1 (K), J11.4 (-12V)
unnamed: J1.1, RV1.3
unnamed: J2.1, RV2.3
unnamed: J3.1, J7.1
unnamed: J4.1, J7.3
unnamed: J5.1, J8.1
unnamed: J6.1, J8.2
unnamed: J7.2, RV1.2
unnamed: J8.4, RV2.2
unnamed: J9.1, R10.1
unnamed: J9.2, R1.2
unnamed: J9.3, R3.1
unnamed: J10.1, R9.1
unnamed: J10.2, R4.1
unnamed: J10.4, R2.2
unnamed: R10.2, R12.1, U1.7
unnamed: R9.2, R11.1, U1.8
unnamed: R7.1, R11.2, U1.9 (-)
unnamed: R8.1, R12.2, U1.6 (-)

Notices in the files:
banana-bread-board-helper/banana-bread-board-helper.kicad_sch:
creativecommons.org/licenses/by/4.0
License: CC BY 4.0
